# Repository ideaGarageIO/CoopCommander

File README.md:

# Coop Monitor

Solar-powered LoRa controller for a chicken coop. It opens the pop door at
sunrise, closes it after sunset, watches temperature, humidity and the
battery, and puts all of it on the farm dashboard and in Home Assistant on
your phone. Built on a Heltec WiFi LoRa 32 V3 plugged into a custom carrier
board, like the gate node.

## Features

### Door control
| Function | What it does |
|---|---|
| **Automatic open / close** | Opens at sunrise and closes after sunset, every day, computed on the node from the coop's latitude / longitude (no internet needed at the coop) |
| **Schedule offsets** | Open N minutes after sunrise, close N minutes after sunset (default +30 min, so late birds get in) |
| **Earliest open time** | Never opens before a set local time (default 06:00), so the flock isn't let out at dawn in midsummer |
| **Auto / Manual mode** | Manual pauses the schedule; the choice survives reboots and power loss |
| **Remote commands** | `OPEN`, `CLOSE`, `STOP`, `AUTO`, `MANUAL` from the dashboard's Coops tab or Home Assistant |
| **Local push button** | On-board PRG button or a weatherproof button on the coop: open → close, and stop while moving |
| **Limit switches** | Motor stops the moment the open or closed switch makes contact |
| **Jam detection** | If a switch isn't reached within the travel timeout, the motor stops and the door reports **JAMMED** (dashboard alert, "door jammed" sensor in Home Assistant) |
| **Safe motor handling** | Pull-downs and firmware keep the motor off during resets; 300 ms pause before every reversal; separate 3 A fuse for the motor |

### Monitoring
| Reading | Shown as |
|---|---|
| Door state | `OPEN`, `CLOSED`, `OPENING`, `CLOSING`, `JAMMED`, `UNKNOWN` |
| Temperature / humidity | DHT22, every 10 s; live charts on the dashboard |
| Battery voltage | 12 V battery through the board's divider |
| Next open / next close | The schedule's upcoming times, plus last opened / last closed |
| Link | Radio signal (RSSI) and online / offline (offline after ~3 min of silence) |
| Local display | OLED shows state, mode, readings and next times; sleeps after 60 s, wakes on a button press or command |

### Dashboard and Home Assistant (no setup needed)
A coop appears automatically the first time it transmits: a **Coops** tile
on the dashboard with controls, charts and an activity log, and in Home
Assistant a door cover, an auto-schedule switch, a door-jammed sensor, and
temperature / humidity / battery / next open / next close sensors. The
dashboard raises alerts for a jammed door, a door still open after dark, low
battery and a coop going offline.

### Power: solar + battery
Every coop runs off grid. A 20 W panel charges a 12 V 10 Ah LiFePO4 battery
through a 10 A charge controller, whose LOAD output feeds the board. The
battery runs the node all night and supplies the door motor; with ~0.6 Ah/day
of load it rides through about **two weeks with no sun**. Sizing, cold-weather
notes and wiring: [docs/power.md](docs/power.md).

### Bench / mock mode
With the default config the node simulates the door (8 s travel) and the
sensor, so you can test the whole system (gateway, dashboard, Home Assistant)
with just a Heltec board on USB.

## How it fits the farm system

| Repo | Role |
|---|---|
| **CoopMonitor** (this repo) | Coop node firmware, carrier PCB, BOM |
| **GateMonitor** | Gate node and the **house gateway**, which bridges every LoRa node (gate and coops) to MQTT and gives the coops the time |
| **Server** | Dashboard, history, Home Assistant integration, home-server deployment |

```
 Coop (solar + 12 V battery)                     House                     Home server
┌──────────────────────────────┐           ┌────────────────┐        ┌──────────────────────┐
│ Heltec V3 on coop carrier    │ LoRa 915  │ House gateway  │  MQTT  │ Mosquitto            │
│  H-bridge -> door motor      │◄─────────►│ (GateMonitor)  │◄──────►│ Farm dashboard       │
│  open/closed limit switches  │   MHz     │ WiFi + NTP     │ coop/  │ Home Assistant       │
│  DHT22, battery, button      │           │ time -> coops  │ <id>/… │  (phone control)     │
└──────────────────────────────┘           └────────────────┘        └──────────────────────┘
```

One gateway serves up to 8 coops. Nothing coop-specific is configured on the
gateway or the server.

## Hardware and BOM

- **Carrier board**: `hardware/pcb/coop_node_carrier`, 110 x 75 mm, 2-layer,
  all through-hole, generated from `scripts/design.py`. See its
  [README](hardware/pcb/coop_node_carrier/README.md) for the pin map,
  connectors and the checks to do before ordering.
- **BOM**: `python3 hardware/pcb/coop_node_carrier/scripts/gen_bom.py` writes
  - `bom_amazon.csv`: carrier board parts (sheet tab *Coop Node Carrier PCB*)
  - `bom_system.csv`: Heltec, antenna, sensors, door motor and driver,
    switches, enclosure, solar panel, battery, charge controller, fusing
    (sheet tab *Coop Monitor*)

  Both match the "Farm IOT Project BOMS" Google Sheet, which also has a power
  budget calculator.

## Getting started

Bench test (bare Heltec, mock door):

```bash
scripts/build.sh coop_node --upload /dev/ttyUSB0
scripts/build.sh coop_node --monitor /dev/ttyUSB0
```

With the house gateway running, `coop-1` shows up on the dashboard within a
minute; OPEN / CLOSE from the dashboard move the simulated door.

Real coop:

1. Copy `config/coops/coop-1.h` to `config/coops/<id>.h` and set the id,
   name, latitude / longitude, time zone, offsets and door travel timeout.
2. `scripts/build.sh coop_node --coop config/coops/<id>.h --upload /dev/ttyUSB0`
3. Wire the solar system, motor and switches, then commission the door:
   [deploy/README.md](deploy/README.md).
4. On the server, set `SIMULATE_DEVICES=false` once real coops exist.

## Repo layout

```
CoopMonitor/
├── firmware/coop_node/     Sketch, sunrise maths, config template, protocol copy
├── firmware/test/          PC unit tests (protocol + schedule)
├── hardware/pcb/coop_node_carrier/   KiCad project, generators, BOM CSVs
├── config/coops/           One config file per coop
├── scripts/                build.sh (arduino-cli in Docker), sync_protocol.sh, host tests
├── deploy/                 Installing and commissioning a coop
├── schematics/             Reference material
└── docs/                   architecture.md (how it works), power.md (solar sizing)
```

## Development

```bash
scripts/test_firmware_host.sh       # protocol + sunrise/sunset unit tests (g++)
scripts/build.sh coop_node          # compile check
scripts/sync_protocol.sh --check    # farm_protocol.h matches GateMonitor's copy
```

The LoRa protocol lives in GateMonitor (`firmware/lib/farm_protocol`); change
it there, then run `scripts/sync_protocol.sh` in both repos.

## Limitations

- No motor-current sensing: jams are caught by the travel timeout, so use a
  gravity-closing door that can't crush a bird.
- The AUX relay output (light / heater) is wired on the board but not yet
  controllable from the dashboard.
- No battery-low lockout: closing the door at night matters more than the
  battery; the charge controller's low-voltage disconnect protects it.

## License

MIT License - See [LICENSE](LICENSE)

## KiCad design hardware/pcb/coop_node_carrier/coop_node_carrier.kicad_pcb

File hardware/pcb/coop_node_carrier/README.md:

# Coop Node Carrier Board (rev A)

Interconnect board for the coop node: a Heltec WiFi LoRa 32 V3 plugs into
female headers, and every off-board module and field wire lands on a
connector. 110 x 75 mm, 2 layers, all through-hole, M3 holes in the corners.

Derived from GateMonitor's `gate_node_carrier`: the 12 V input chain, battery
sense, limit-switch conditioning, DHT22 terminal and Heltec footprint are the
same circuit (and the same verified Heltec geometry). The coop board swaps the
two gate relays for an H-bridge motor connection with its own fused supply,
keeps one relay channel as AUX, and adds an external button input.

KiCad 6 project, **generated** from `scripts/design.py`:

```bash
cd hardware/pcb/coop_node_carrier/scripts
python3 gen_schematic.py     # -> coop_node_carrier.kicad_sch
python3 gen_pcb.py --check   # placement sanity check only
python3 gen_pcb.py           # -> coop_node_carrier.kicad_pcb (+ net classes in .kicad_pro)
python3 gen_bom.py           # -> bom_amazon.csv (board parts + off-board modules)
python3 gen_3d.py            # -> coop_node.3dshapes/ placeholder models
```

`gen_pcb.py` needs KiCad's `pcbnew` Python module (`sudo apt install kicad`).
Regenerating the PCB **overwrites routing**: once you route in KiCad, treat
the `.kicad_pcb` as hand-edited and use *Tools → Update PCB from Schematic*.

## Block diagram

```
12V battery ─ J6 ─┬─ F1 0.5A ─ D1 1N5819 ─ VIN ─┬─ U1 Mini360 ─ D3 ─ +5V ─ Heltec 5V
                  │                             ├─ D2 P6KE18CA, C1 100µF, C2 100nF
                  │  (BATT_F) R1 100k / R2 22k ─ BATT_ADC (GPIO2)
                  │
                  └─ F2 3A ─ D6 1N5822 ─ MOTOR_VM ─┬─ C8 100µF ─ J10 ─► H-bridge VM/GND
                                                   (1.5 mm "Motor" net class)
Heltec 3V3 ─┬─ J3 MOTOR CTRL (3V3 / GND / IN1 GPIO7 / IN2 GPIO4, 10k pull-downs R10/R11)
            ├─ R3/R5 10k ─ J7 limit switches (1k + 100nF, P6KE6.8CA) ─ GPIO5 / GPIO6
            ├─ R8 10k ─ J11 button (1k + 100nF, P6KE6.8CA) ─ GPIO33
            ├─ JP1 (1-2) ─ RELAY_VCC ─ J5 AUX relay module (IN = GPIO47)
            └─ J8 DHT22 (+ R7 10k) GPIO48, J9 expansion (GPIO34)
```

## Pin map (firmware must match)

| Net | GPIO | Connector |
|---|---|---|
| LIM_OPEN | 5 | J7-1 |
| LIM_CLOSED | 6 | J7-2 |
| MOTOR_IN1 | 7 | J3-3 |
| MOTOR_IN2 | 4 | J3-4 |
| AUX_RELAY | 47 | J5-3 |
| BATT_ADC | 2 | R1/R2 divider (ratio 5.545) |
| DHT_DATA | 48 | J8-2 |
| BTN_EXT | 33 | J11-1 (via R9) |
| EXP_IO34 | 34 | J9-2 |

## Connectors

| Ref | Label | Pins | To |
|---|---|---|---|
| J6 | 12V BATT | 12V+ / GND | Battery (through the charge controller's load output) |
| J10 | DRIVER PWR | VM / GND | H-bridge module motor supply |
| J3 | MOTOR CTRL | 3V3 / GND / IN1 / IN2 | H-bridge module logic (JST-XH 4) |
| J8 | DHT22 | + / DATA / - | DHT22 |
| J7 | LIMITS | OPEN / CLOSED / GND | Two dry-contact limit switches |
| J11 | BUTTON | BTN / GND | Momentary push button |
| J5 | AUX RELAY | DC+ / DC- / IN | Relay module (JST-XH 3) |
| J9 | EXPANSION | 3V3 / IO34 / GND | Spare |

The motor itself wires to the H-bridge module's output terminals, not to this
board.

## BOM

`python3 scripts/gen_bom.py` writes two CSVs whose columns match the
"Farm IOT Project BOMS" Google Sheet:

- `bom_amazon.csv` → tab **Coop Node Carrier PCB**: the board's parts grouped
  into purchase lines. Parts shared with the gate carrier reuse the product
  links and pack prices already chosen for it.
- `bom_system.csv` → tab **Coop Monitor**: Heltec, antenna, Mini360, DHT22,
  enclosure, door motor + DRV8871 driver, limit switches, button, and the
  solar system (20 W panel, 12 V 10 Ah LiFePO4, 10 A PWM controller, fuse).
  Sizing in [docs/power.md](../../../docs/power.md).

New parts have a blank SKU price: fill it in from the listing in the sheet.

## VERIFY before ordering boards

1. **Heltec geometry and pin order**: same as the gate carrier, which was
   checked against Heltec's datasheet. Still caliper-check one board.
2. **MF-RHT300 footprint / lead pitch**: the KiCad footprint is Bourns
   MF-RHT300. An RXEF300 (30 V) is a better voltage match for a charging 12 V
   system; check its lead pitch fits the footprint, or pick its footprint.
3. **1N5822 lead bend**: DO-201AD with 15.24 mm pitch. Check your diodes' body
   length.
4. **H-bridge module wiring**: J3 assumes 3V3 / GND / IN1 / IN2. Crimp the
   cable to match your module's header (a DRV8871 breakout needs only GND /
   IN1 / IN2; leave 3V3 unconnected).
5. **Motor current**: F2 holds 3 A and D6 is a 3 A diode. A motor that stalls
   above ~3 A will trip F2. Measure the stall current of your motor.
6. **Limit switches and button must be dry contacts to GND.**
7. Open the schematic and run **ERC**. Open the PCB, route it, run **DRC**, and
   check the parts in the 3D viewer.

## Notes

- D6 drops ~0.5 V at 2 A (~1 W). Leave space around it; don't bury it under the
  Heltec.
- The 1N5819 + 0.5 A fuse logic path is kept separate from the motor path, so
  a stalled motor trips F2 without browning out the ESP32.
- Mount the DHT22 inside the coop away from the heat lamp, or under the eaves
  outside, using the J8 terminal.

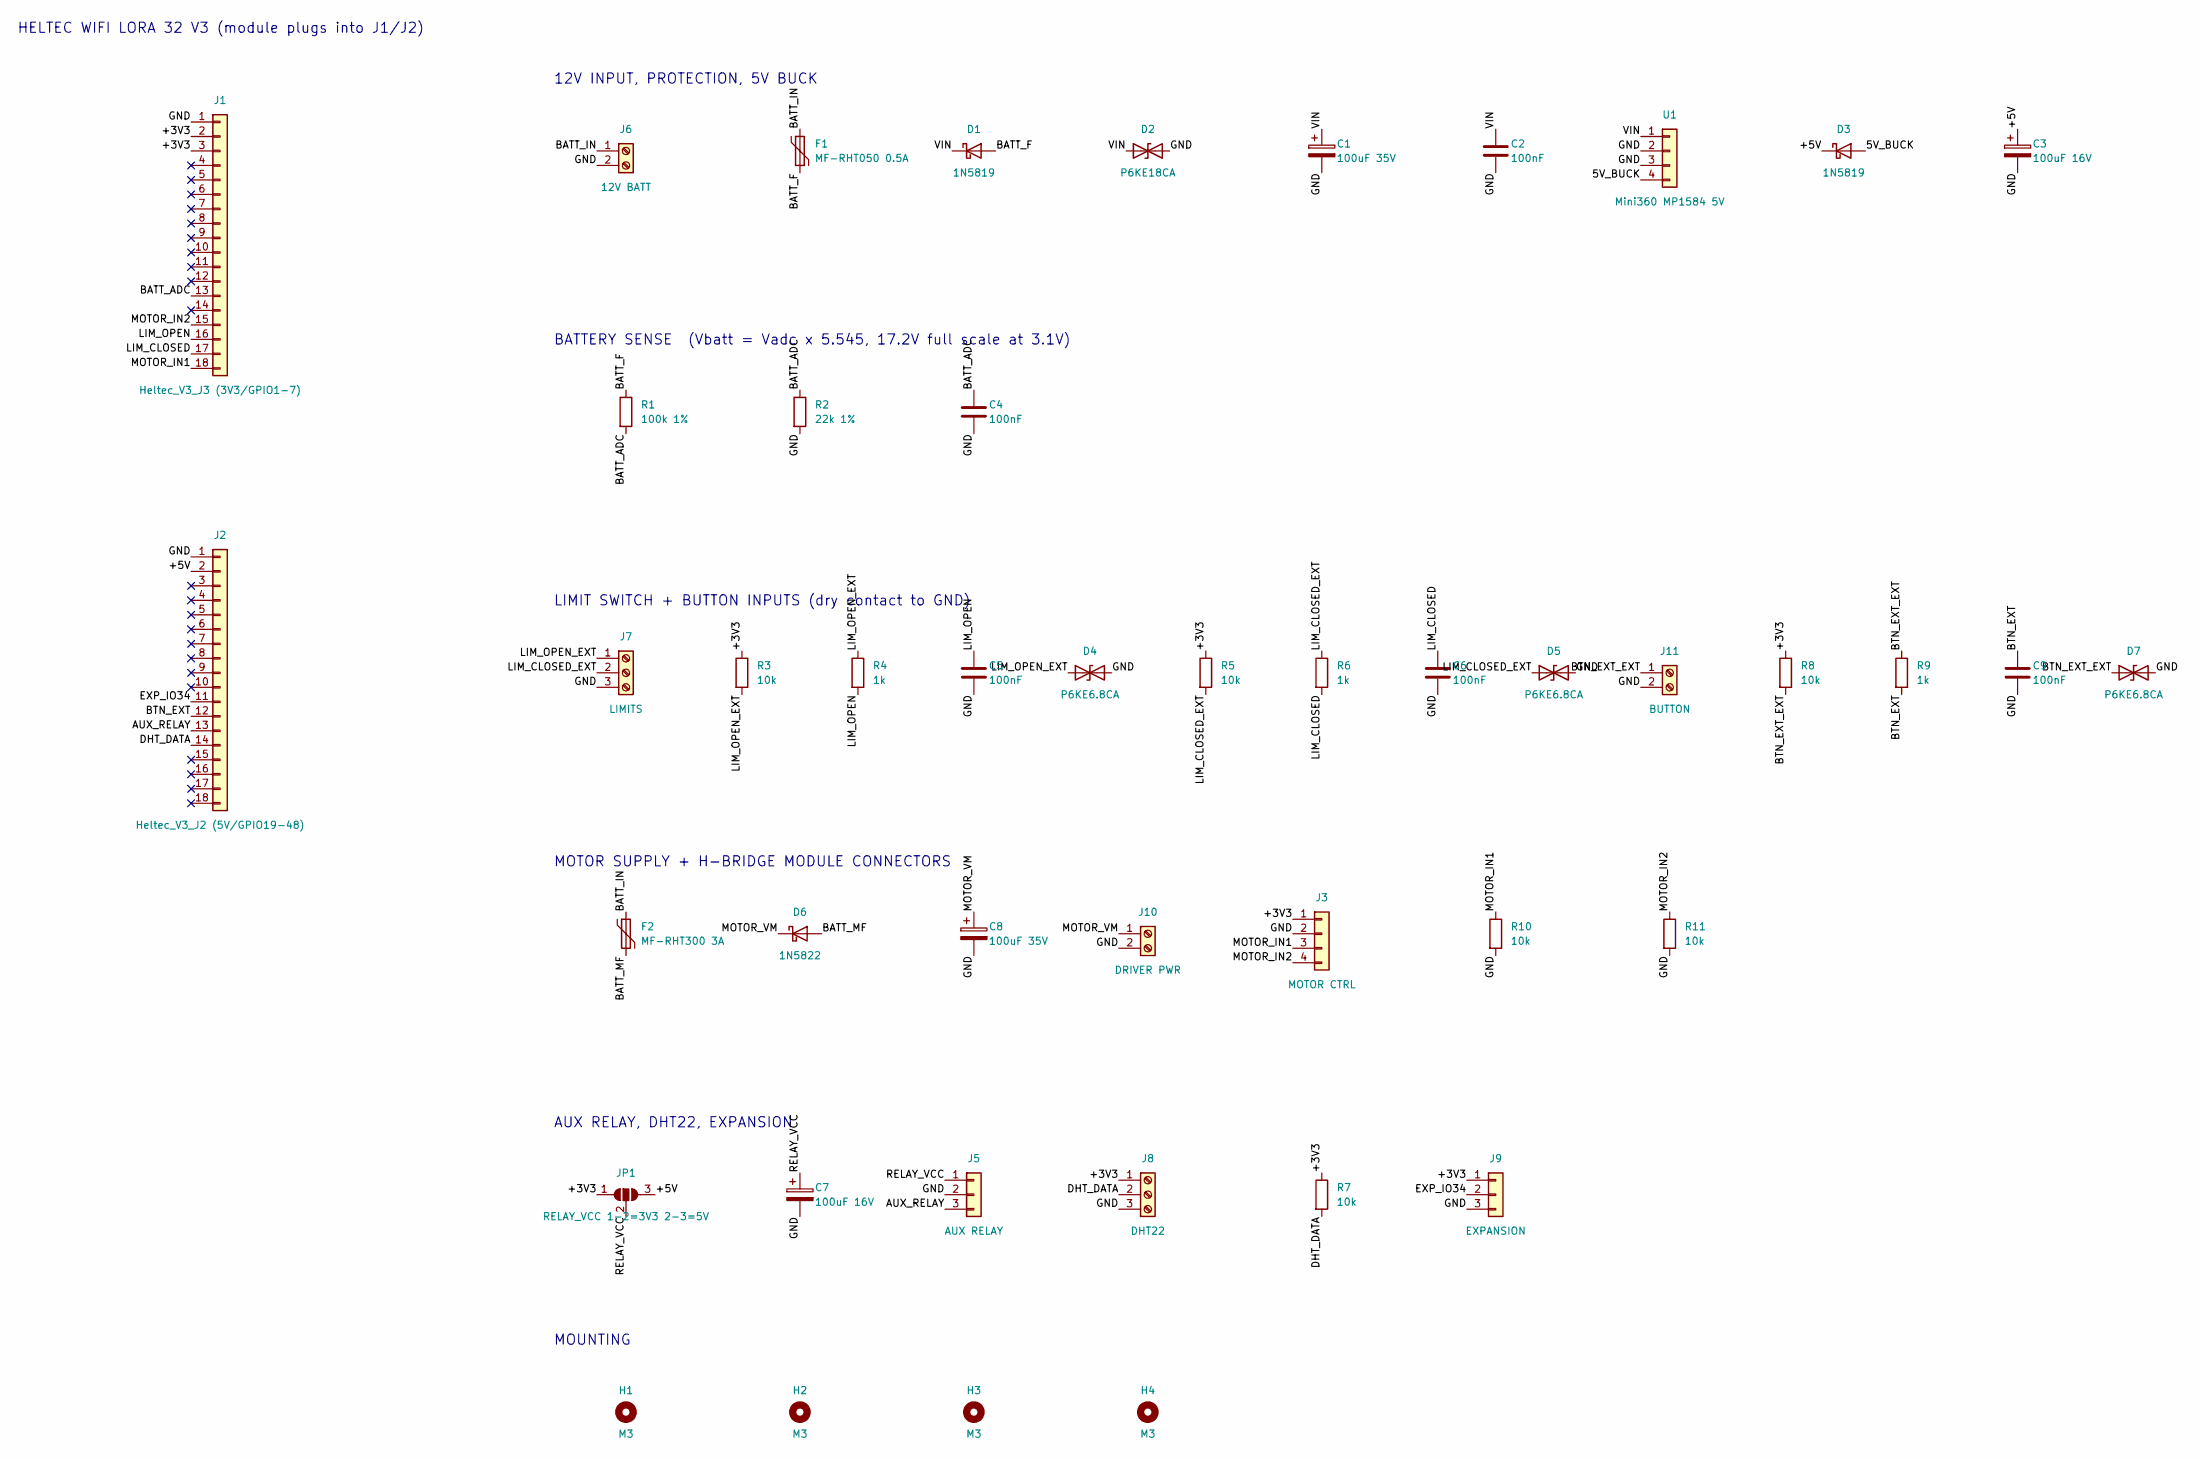
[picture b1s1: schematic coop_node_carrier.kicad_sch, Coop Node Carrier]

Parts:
C1, C8: 100uF 35V; CP_Radial_D6.3mm_P2.50mm
C2, C4, C5, C6, C9: 100nF; C_Disc_D5.0mm_W2.5mm_P5.00mm
C3, C7: 100uF 16V; CP_Radial_D6.3mm_P2.50mm
D1, D3: 1N5819; D_DO-41_SOD81_P10.16mm_Horizontal
D2: P6KE18CA; D_DO-15_P10.16mm_Horizontal
D4, D5, D7: P6KE6.8CA; D_DO-15_P10.16mm_Horizontal
D6: 1N5822; D_DO-201AD_P15.24mm_Horizontal
F1: MF-RHT050 0.5A; Fuse_Bourns_MF-RHT050
F2: MF-RHT300 3A; Fuse_Bourns_MF-RHT300
H1, H2, H3, H4: M3; MountingHole_3.2mm_M3
J1: Heltec_V3_J3 (3V3/GPIO1-7); PinSocket_1x18_P2.54mm_Vertical
J2: Heltec_V3_J2 (5V/GPIO19-48); PinSocket_1x18_P2.54mm_Vertical
J3: MOTOR CTRL; JST_XH_B4B-XH-A_1x04_P2.50mm_Vertical
J5: AUX RELAY; JST_XH_B3B-XH-A_1x03_P2.50mm_Vertical
J6: 12V BATT; TerminalBlock_Phoenix_MKDS-1,5-2-5.08_1x02_P5.08mm_Horizont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
J7: LIMITS; TerminalBlock_Phoenix_MKDS-1,5-3-5.08_1x03_P5.08mm_Horizont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
J8: DHT22; TerminalBlock_Phoenix_MKDS-1,5-3-5.08_1x03_P5.08mm_Horizont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
J9: EXPANSION; PinHeader_1x03_P2.54mm_Vertical
J10: DRIVER PWR; TerminalBlock_Phoenix_MKDS-1,5-2-5.08_1x02_P5.08mm_Horizont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
J11: BUTTON; TerminalBlock_Phoenix_MKDS-1,5-2-5.08_1x02_P5.08mm_Horizont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
JP1: RELAY_VCC 1-2=3V3 2-3=5V; SolderJumper-3_P1.3mm_Open_RoundedPad1.0x1.5mm
R1: 100k 1%; R_Axial_DIN0207_L6.3mm_D2.5mm_P7.62mm_Horizontal
R2: 22k 1%; R_Axial_DIN0207_L6.3mm_D2.5mm_P7.62mm_Horizontal
R3, R5, R7, R8, R10, R11: 10k; R_Axial_DIN0207_L6.3mm_D2.5mm_P7.62mm_Horizontal
R4, R6, R9: 1k; R_Axial_DIN0207_L6.3mm_D2.5mm_P7.62mm_Horizontal
U1: Mini360 MP1584 5V; Mini360_MP1584

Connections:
5V_BUCK: D3.2 (A), U1.4
+3V3: J1.2, J1.3, J3.1, J8.1, J9.1, JP1.1 (A), R3.1, R5.1, R7.1, R8.1
+5V: C3.1, D3.1 (K), J2.2, JP1.3 (B)
AUX_RELAY: J2.13, J5.3
BATT_ADC: C4.1, J1.13, R1.2, R2.1
BATT_F: D1.2 (A), F1.2, R1.1
BATT_IN: F1.1, F2.1, J6.1
BATT_MF: D6.2 (A), F2.2
BTN_EXT: C9.1, J2.12, R9.2
BTN_EXT_EXT: D7.1 (A1), J11.1, R8.2, R9.1
DHT_DATA: J2.14, J8.2, R7.2
EXP_IO34: J2.11, J9.2
GND: C1.2, C2.2, C3.2, C4.2, C5.2, C6.2, C7.2, C8.2, C9.2, D2.2 (A2), D4.2 (A2), D5.2 (A2), D7.2 (A2), J1.1, J2.1, J3.2, J5.2, J6.2, J7.3, J8.3, J9.3, J10.2, J11.2, R2.2, R10.2, R11.2, U1.2, U1.3
LIM_CLOSED: C6.1, J1.17, R6.2
LIM_CLOSED_EXT: D5.1 (A1), J7.2, R5.2, R6.1
LIM_OPEN: C5.1, J1.16, R4.2
LIM_OPEN_EXT: D4.1 (A1), J7.1, R3.2, R4.1
MOTOR_IN1: J1.18, J3.3, R10.1
MOTOR_IN2: J1.15, J3.4, R11.1
MOTOR_VM: C8.1, D6.1 (K), J10.1
RELAY_VCC: C7.1, J5.1, JP1.2 (C)
VIN: C1.1, C2.1, D1.1 (K), D2.1 (A1), U1.1

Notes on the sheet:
HELTEC WIFI LORA 32 V3 (module plugs into J1/J2)
12V INPUT, PROTECTION, 5V BUCK
BATTERY SENSE (Vbatt = Vadc x 5.545, 17.2V full scale at 3.1V)
LIMIT SWITCH + BUTTON INPUTS (dry contact to GND)
MOTOR SUPPLY + H-BRIDGE MODULE CONNECTORS
AUX RELAY, DHT22, EXPANSION
MOUNTING

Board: 2 copper layers, 45 parts (0 on the bottom side), 22 nets, no tracks yet.

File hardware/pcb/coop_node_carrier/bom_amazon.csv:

Component,Description,Link,Required SKU,Units per SKU,SKU Price,Price Per Unit,Required Units,Price Per Build,Total Price,Board Refs,Typical Pack
Female pin header 2.54mm,1x40 straight female header strip; cut into 2x 1x18 for the Heltec (cutting loses 1 pin),https://www.amazon.com/dp/B00VVI1L1W,1,10,5.99,,1,,,J1 J2,10-20 strips
Male pin header 2.54mm,1x40 breakaway male header; 1x3 for J9 plus 4 single pins to stand the Mini360 off the board,https://www.amazon.com/dp/B0FRZW75VS,1,20,6.29,,1,,,J9,10-40 strips
JST-XH 3-pin PCB header,JST-XH 2.54mm 3-pin shrouded vertical through-hole header (B3B-XH-A style); kit also includes housings and crimp terminals,https://www.amazon.com/dp/B0B2R99X99,1,50,6.39,,1,,,J5,50 headers
JST-XH 3-pin to Dupont cable,"20cm 24AWG, JST-XH 3-pin housing to 3x Dupont female, for the AUX relay module",https://www.amazon.com/dp/B0GX9GBVN8,1,12,9.99,,1,,,J5,12 cables
JST-XH 4-pin PCB header,"JST-XH 2.5mm 4-pin vertical through-hole header (B4B-XH-A style), for the H-bridge module",https://www.amazon.com/s?k=JST+XH+4+pin+pcb+header+B4B-XH-A+kit,1,,,,1,,,J3,kit
JST-XH 4-pin to Dupont cable,JST-XH 4-pin housing to 4x Dupont female (3V3 / GND / IN1 / IN2) for the H-bridge module; or crimp one from the header kit,https://www.amazon.com/s?k=JST+XH+4+pin+to+dupont+female+cable,1,,,,1,,,J3,10 cables
Screw terminal 5.08mm 2-pos,"PCB screw terminal, 5.08mm pitch, 2 position (KF301-2P / MKDS style)",https://www.amazon.com/dp/B0DPYDRNF7,1,60,7.98,,3,,,J6 J10 J11,assortment
Screw terminal 5.08mm 3-pos,"PCB screw terminal, 5.08mm pitch, 3 position (KF301-3P / MKDS style)",https://www.amazon.com/dp/B0H8SPXGCM,1,10,7.19,,2,,,J7 J8,assortment
PTC resettable fuse 0.5A,"Radial PPTC, 0.5A hold / 1A trip, >=30V (RXEF050, MF-R050 or equivalent), 5mm lead pitch. Logic supply",https://www.amazon.com/dp/B07969FY8X,1,10,5.98,,1,,,F1,10-50
PTC resettable fuse 3A,"Radial PPTC, 3A hold / 6A trip, >=16V (RXEF300 30V preferred, MF-RHT300), ~5mm lead pitch. Motor supply",https://www.amazon.com/s?k=RXEF300+PPTC+resettable+fuse+3A+radial,1,,,,1,,,F2,10-20
Schottky diode 1N5819,"1N5819, 40V 1A, DO-41 axial",https://www.amazon.com/dp/B0FC2CWKPL,1,150,7.99,,2,,,D1 D3,20-100
Schottky diode 1N5822,"1N5822, 40V 3A, DO-201AD axial. Motor supply reverse-polarity protection",https://www.amazon.com/s?k=1N5822+schottky+diode+3A+DO-201AD,1,,,,1,,,D6,10-50
TVS diode P6KE18CA,"P6KE18CA, 600W bidirectional, 15.3V standoff, DO-15 axial",https://www.amazon.com/dp/B0GX6MC3RH,1,20,4.19,,1,,,D2,10-50
TVS diode P6KE6.8CA,"P6KE6.8CA (P6KE6V8CA), 600W bidirectional, 5.8V standoff, DO-15 axial",https://www.amazon.com/dp/B079KJ6LND,1,50,5.99,,3,,,D4 D5 D7,10-50
Electrolytic cap 100uF 35V,"100uF 35V radial, 6.3mm diameter, 2.5mm lead pitch, 105C (35V covers the 16V positions too)",https://www.amazon.com/dp/B0GTXVDWBK,1,50,5.69,,4,,,C1 C3 C7 C8,20-100
Ceramic cap 100nF,"100nF (104) 50V ceramic, radial, 5.08mm lead pitch",https://www.amazon.com/dp/B08B3VCK42,1,120,6.99,,5,,,C2 C4 C5 C6 C9,50-100
Resistor kit 1% metal film 1/4W,"1/4W 1% metal film, 6.3mm body. Needs 1k, 10k, 22k, 100k; one kit covers every build (1x 100k, 6x 10k, 3x 1k, 1x 22k)",https://www.amazon.com/dp/B0FT362FV2,1,1,7.99,,1,,,R1 R2 R3 R4 R5 R6 R7 R8 R9 R10 R11,kit

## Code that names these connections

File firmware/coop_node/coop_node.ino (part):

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// Must match hardware/pcb/coop_node_carrier/scripts/design.py
#define PIN_LIMIT_OPEN    5     // J7-1, active LOW (dry contact to GND)
#define PIN_LIMIT_CLOSED  6     // J7-2, active LOW
#define PIN_MOTOR_IN1     7     // J3-3 -> H-bridge IN1
#define PIN_MOTOR_IN2     4     // J3-4 -> H-bridge IN2
#define PIN_AUX_RELAY     47    // J5 relay module (light / heater), held off
#define PIN_BATTERY_ADC   2     // R1/R2 divider
#define PIN_DHT_DATA      48    // J8-2
#define PIN_BTN_EXT       33    // J11 external push button, active LOW
#define PIN_BTN_PRG       0     // On-board PRG button, active LOW

// ---------------------------------------------------------------- timing
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
// ---------------------------------------------------------------- state
static SSD1306Wire display(0x3c, 500000, SDA_OLED, SCL_OLED, GEOMETRY_128_64, RST_OLED);
static DHT dht(PIN_DHT_DATA, DHT22);
static Preferences prefs;

enum MotorDir : uint8_t { DIR_NONE, DIR_OPEN, DIR_CLOSE };
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    bool rawPrev;
    unsigned long rawSince;
};
static Button buttons[] = {{PIN_BTN_PRG, false, false, 0}, {PIN_BTN_EXT, false, false, 0}};

// Link / messaging
static uint16_t sequenceNum = 0;
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// ---------------------------------------------------------------- setup / loop
void setup() {
    // Motor off before anything else, so a reset never leaves it running
    pinMode(PIN_MOTOR_IN1, OUTPUT);
    pinMode(PIN_MOTOR_IN2, OUTPUT);
    digitalWrite(PIN_MOTOR_IN1, LOW);
    digitalWrite(PIN_MOTOR_IN2, LOW);

    Serial.begin(115200);
    delay(300);
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void initGPIO() {
    pinMode(PIN_LIMIT_OPEN, INPUT_PULLUP);
    pinMode(PIN_LIMIT_CLOSED, INPUT_PULLUP);
    pinMode(PIN_BTN_EXT, INPUT_PULLUP);
    pinMode(PIN_BTN_PRG, INPUT_PULLUP);
    pinMode(PIN_AUX_RELAY, OUTPUT);
    digitalWrite(PIN_AUX_RELAY, LOW);
    analogReadResolution(12);
    analogSetPinAttenuation(PIN_BATTERY_ADC, ADC_11db);
}
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void motorDrive(MotorDir dir) {
    bool forward = (dir == DIR_OPEN) != MOTOR_REVERSED;
    if (dir == DIR_NONE) {
        digitalWrite(PIN_MOTOR_IN1, LOW);   // Both low = coast
        digitalWrite(PIN_MOTOR_IN2, LOW);
    } else {
        digitalWrite(PIN_MOTOR_IN1, forward ? HIGH : LOW);
        digitalWrite(PIN_MOTOR_IN2, forward ? LOW : HIGH);
    }
}

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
